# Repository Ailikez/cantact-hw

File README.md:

# CANtact Hardware

Add isolated version in [CAN Isolated](https://github.com/x893/cantact-hw/tree/master/CAN Isolated) folder.

This repository contains the hardware design files for the CANtact tool. They 
can be opened and edited with [KiCad](http://www.kicad-pcb.org/).

A PDF of the schematic is available
[here](https://github.com/CANtact/cantact-hw/blob/master/cantact.pdf?raw=true).

## License

Hardware files released under the [Creative Commons Attribution-ShareAlike 4.0
International License](http://creativecommons.org/licenses/by-sa/4.0/) (CC BY-SA
4.0)

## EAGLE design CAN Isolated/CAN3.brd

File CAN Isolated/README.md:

# CANtact Hardware with isolated CAN

This repository contains the hardware design files for the isolated CANtact tool.
They can be opened and edited with [CADSoft Eagle](http://www.cadsoft.de/).

A PDF of the schematics is available
[CAN1](https://github.com/x893/cantact-hw/blob/master/CAN Isolated/CAN1.pdf?raw=true)
and
[CAN2](https://github.com/x893/cantact-hw/blob/master/CAN Isolated/CAN2.pdf?raw=true)

## License

Hardware files released under the [Creative Commons Attribution-ShareAlike 4.0
International License](http://creativecommons.org/licenses/by-sa/4.0/) (CC BY-SA
4.0)

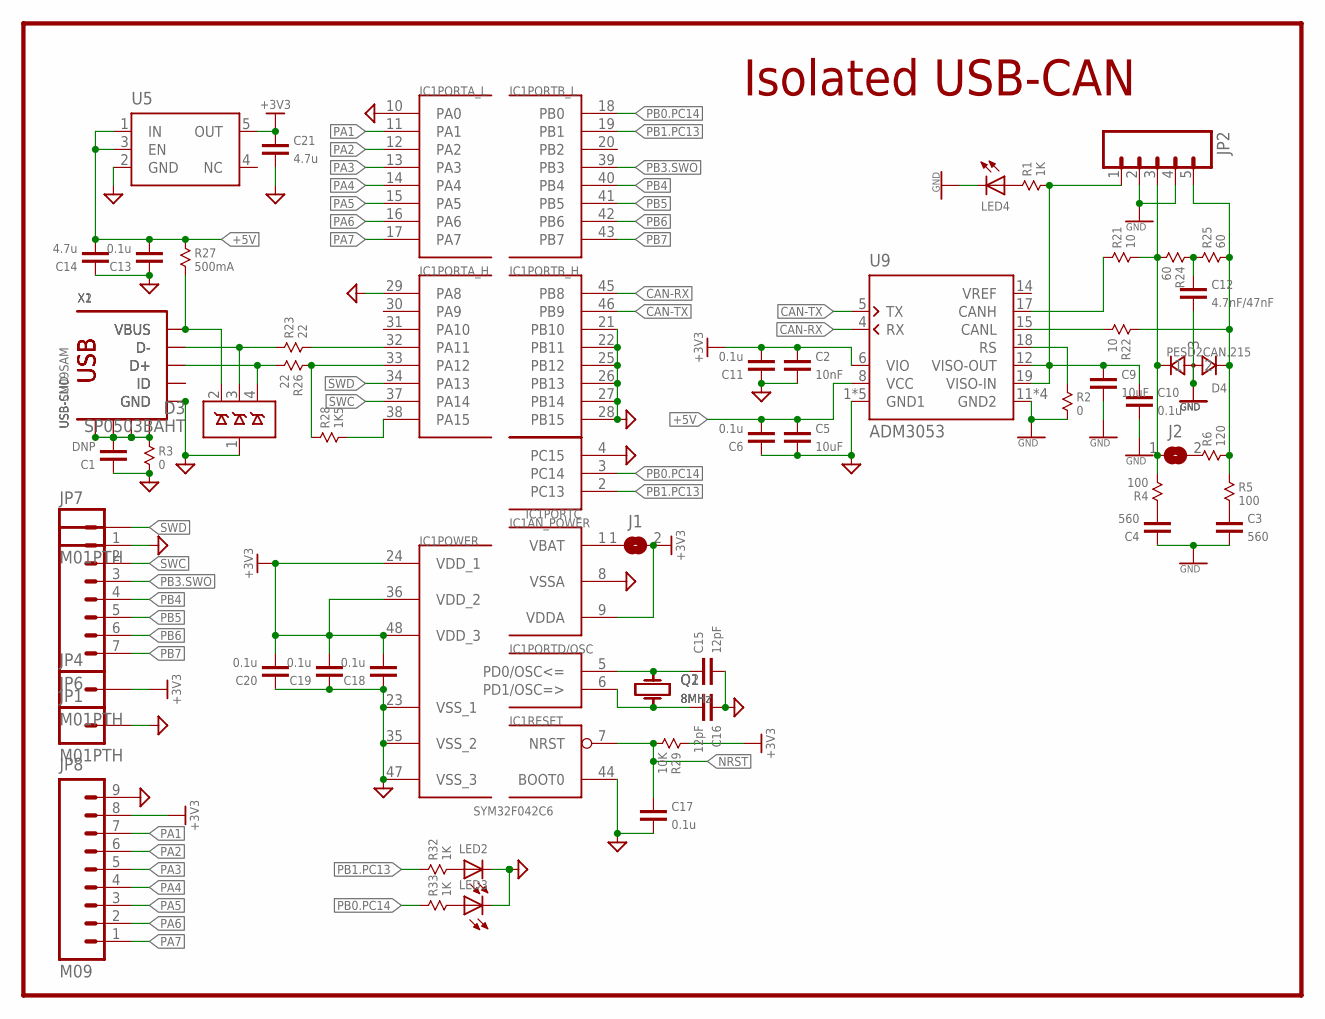
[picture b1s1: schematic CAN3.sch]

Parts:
C1: DNP; 0603
C2: 10nF; 0603
C3, C4: 560; 0603
C5, C9: 10uF; 0805
C6, C10, C11, C13, C17, C18, C19, C20: 0.1u; 0603
C12: 4.7nF/47nF; 0603
C14, C21: 4.7u; 0603
C15, C16: 12pF; 0603
D3: SP0503BAHT; SOT143
D4: PESD2CAN.215; SOT-23
IC1: SYM32F042C6; TQFP48
J1, J2: JUMPER2-0402
JP1, JP4, JP7: M01PTH; 1X01
JP2: M05PTH; 1X05
JP6: M07; 1X07
JP8: M09; 1X09
LED2, LED3, LED4: LEDCHIPLED_0603; CHIPLED_0603
Q1: 8MHz; KX-9A
Q2: 8MHz; KX-7
R1, R32, R33: 1K; 0603
R2, R3: 0; 0603
R4, R5: 100; 0603
R6: 120; 0603
R21, R22: 10; 0603
R23, R26: 22; 0603
R24, R25: 60; 0603
R27: 500mA; 0805
R28: 1K5; 0603
R29: 10K; 0603
U5: TPS73033; SOT23-5
U9: ADM3053; SO20W
X1: USB-SMD; USB-MINIB
X2: USB-CU09SAM; CU09SAM

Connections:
+3V3: C2.2, C11.1, C18.1, C19.1, C20.1, C21.2, IC1.9 (VDDA), IC1.24 (VDD_1), IC1.36 (VDD_2), IC1.48 (VDD_3), J1.2, JP4.1, JP8.8, R29.1, U5.5 (OUT), U9.6 (VIO)
+5V: C5.2, C6.1, C13.1, C14.1, R27.1, U5.1 (IN), U5.3 (EN), U9.8 (VCC)
CAN-H: D4.1, J2.1, JP2.3, R4.2, R21.2, R24.2
CAN-L: D4.2, JP2.5, R5.1, R6.2, R22.1, R25.2
CAN-RX: IC1.45 (PB8), U9.4 (RX)
CAN-TX: IC1.46 (PB9), U9.5 (TX)
CANH: R21.1, U9.17 (CANH)
CANL: R22.2, U9.15 (CANL)
GNDA: C3.1, C4.2, C9.1, C10.1, C12.1, D4.3, JP2.2, JP2.4, LED4.C, R2.2, U9.11 (GND2), U9.13 (GND2), U9.16 (GND2), U9.20 (GND2)
GNDD: C1.2, C2.1, C5.1, C6.2, C11.2, C13.2, C14.2, C15.1, C16.2, C17.1, C18.2, C19.2, C20.2, C21.1, D3.1 (GND), IC1.4 (PC15), IC1.8 (VSSA), IC1.10 (PA0), IC1.21 (PB10), IC1.22 (PB11), IC1.23 (VSS_1), IC1.25 (PB12), IC1.26 (PB13), IC1.27 (PB14), IC1.28 (PB15), IC1.29 (PA8), IC1.35 (VSS_2), IC1.44 (BOOT0), IC1.47 (VSS_3), JP1.1, JP6.1, JP8.9, LED2.C, LED3.C, R3.2, U5.2 (GND), U9.1 (GND1), U9.3 (GND1), U9.7 (GND1), U9.9 (GND1), U9.10 (GND1), X1.GND, X2.5 (GND)
unnamed: LED4.A, R1.1
unnamed: R2.1, U9.18 (RS)
unnamed: C12.2, R24.1, R25.1
unnamed: X1.ID, X2.4 (ID)
unnamed: C1.1, R3.1, X1.GND@1 (GND), X1.GND@2 (GND), X1.GND@3 (GND), X1.GND@4 (GND), X2.GND@1 (GND), X2.GND@2 (GND), X2.GND@3 (GND), X2.GND@4 (GND)
unnamed: IC1.1 (VBAT), J1.1
unnamed: IC1.32 (PA11), R23.2
unnamed: LED2.A, R32.2
unnamed: C3.2, R5.2
unnamed: C4.1, R4.1
unnamed: J2.2, R6.1
unnamed: LED3.A, R33.2
unnamed: IC1.33 (PA12), R26.1, R28.1
unnamed: D3.4 (D3), R26.2, X1.D+, X2.3 (D+)
unnamed: D3.3 (D2), R23.1, X1.D-, X2.2 (D-)
unnamed: D3.2 (D1), R27.2, X1.VBUS, X2.1 (VBUS)
unnamed: IC1.38 (PA15), R28.2
unnamed: C15.2, IC1.5 (PD0/OSC<=), Q1.1, Q2.1
unnamed: C16.1, IC1.6 (PD1/OSC=>), Q1.3 (2), Q2.3 (2)
NRST: C17.2, IC1.7 (NRST), R29.2
PA1: IC1.11 (PA1), JP8.7
PA2: IC1.12 (PA2), JP8.6
PA3: IC1.13 (PA3), JP8.5
PA4: IC1.14 (PA4), JP8.4
PA5: IC1.15 (PA5), JP8.3
PA6: IC1.16 (PA6), JP8.2
PA7: IC1.17 (PA7), JP8.1
PB0.PC14: IC1.3 (PC14), IC1.18 (PB0), R33.1
PB1.PC13: IC1.2 (PC13), IC1.19 (PB1), R32.1
PB3.SWO: IC1.39 (PB3), JP6.3
PB4: IC1.40 (PB4), JP6.4
PB5: IC1.41 (PB5), JP6.5
PB6: IC1.42 (PB6), JP6.6
PB7: IC1.43 (PB7), JP6.7
SWC: IC1.37 (PA14), JP6.2
SWD: IC1.34 (PA13), JP7.1
VCC2: C9.2, C10.2, JP2.1, R1.2, U9.12 (VISO-OUT), U9.19 (VISO-IN)

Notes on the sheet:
Isolated USB-CAN

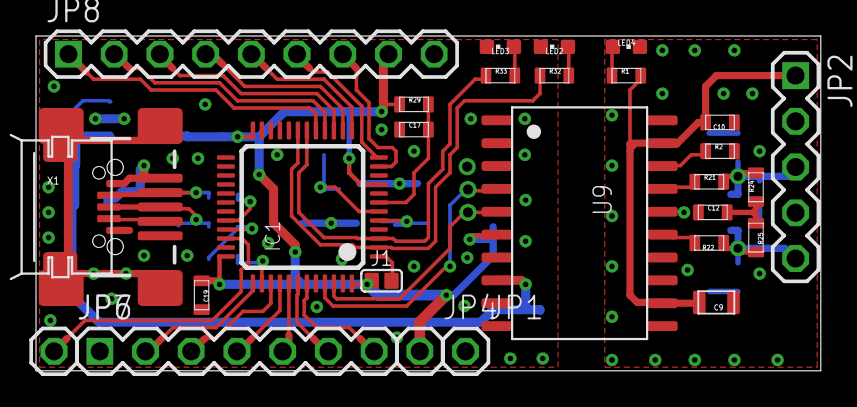
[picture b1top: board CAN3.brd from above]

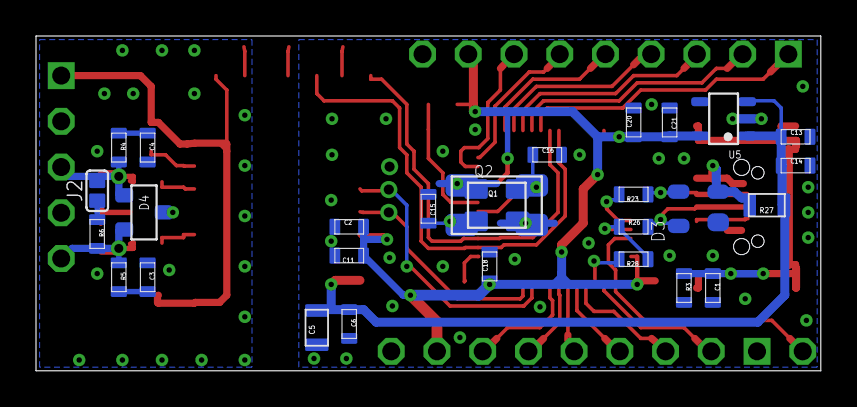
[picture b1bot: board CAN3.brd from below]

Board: 2 copper layers, 43.6 x 18.6 mm, 56 parts (28 on the bottom side), 47 nets.

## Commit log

2015-07-24 Add isolated CAN version with DC-DC and solid power.
2015-09-21 Add CAN3 with ADM3053

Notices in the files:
parts and their libraries:
SparkFun-Aesthetics: Licensing: CC v3.0 Share-Alike You are welcome to use this library for commercial purposes.
TL-WR703N: Copyright © 2012, Michel Stempin, All rights reserved
Licenced under Creative Commons CC BY-SA 3.0 license.
